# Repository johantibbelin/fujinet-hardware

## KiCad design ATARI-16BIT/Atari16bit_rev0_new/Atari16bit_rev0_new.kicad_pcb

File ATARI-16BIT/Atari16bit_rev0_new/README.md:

# Fujinet Atari 16-bit rev0

Schematic for Atari 16-bit Fujinet prototype. No board layout is done yet.

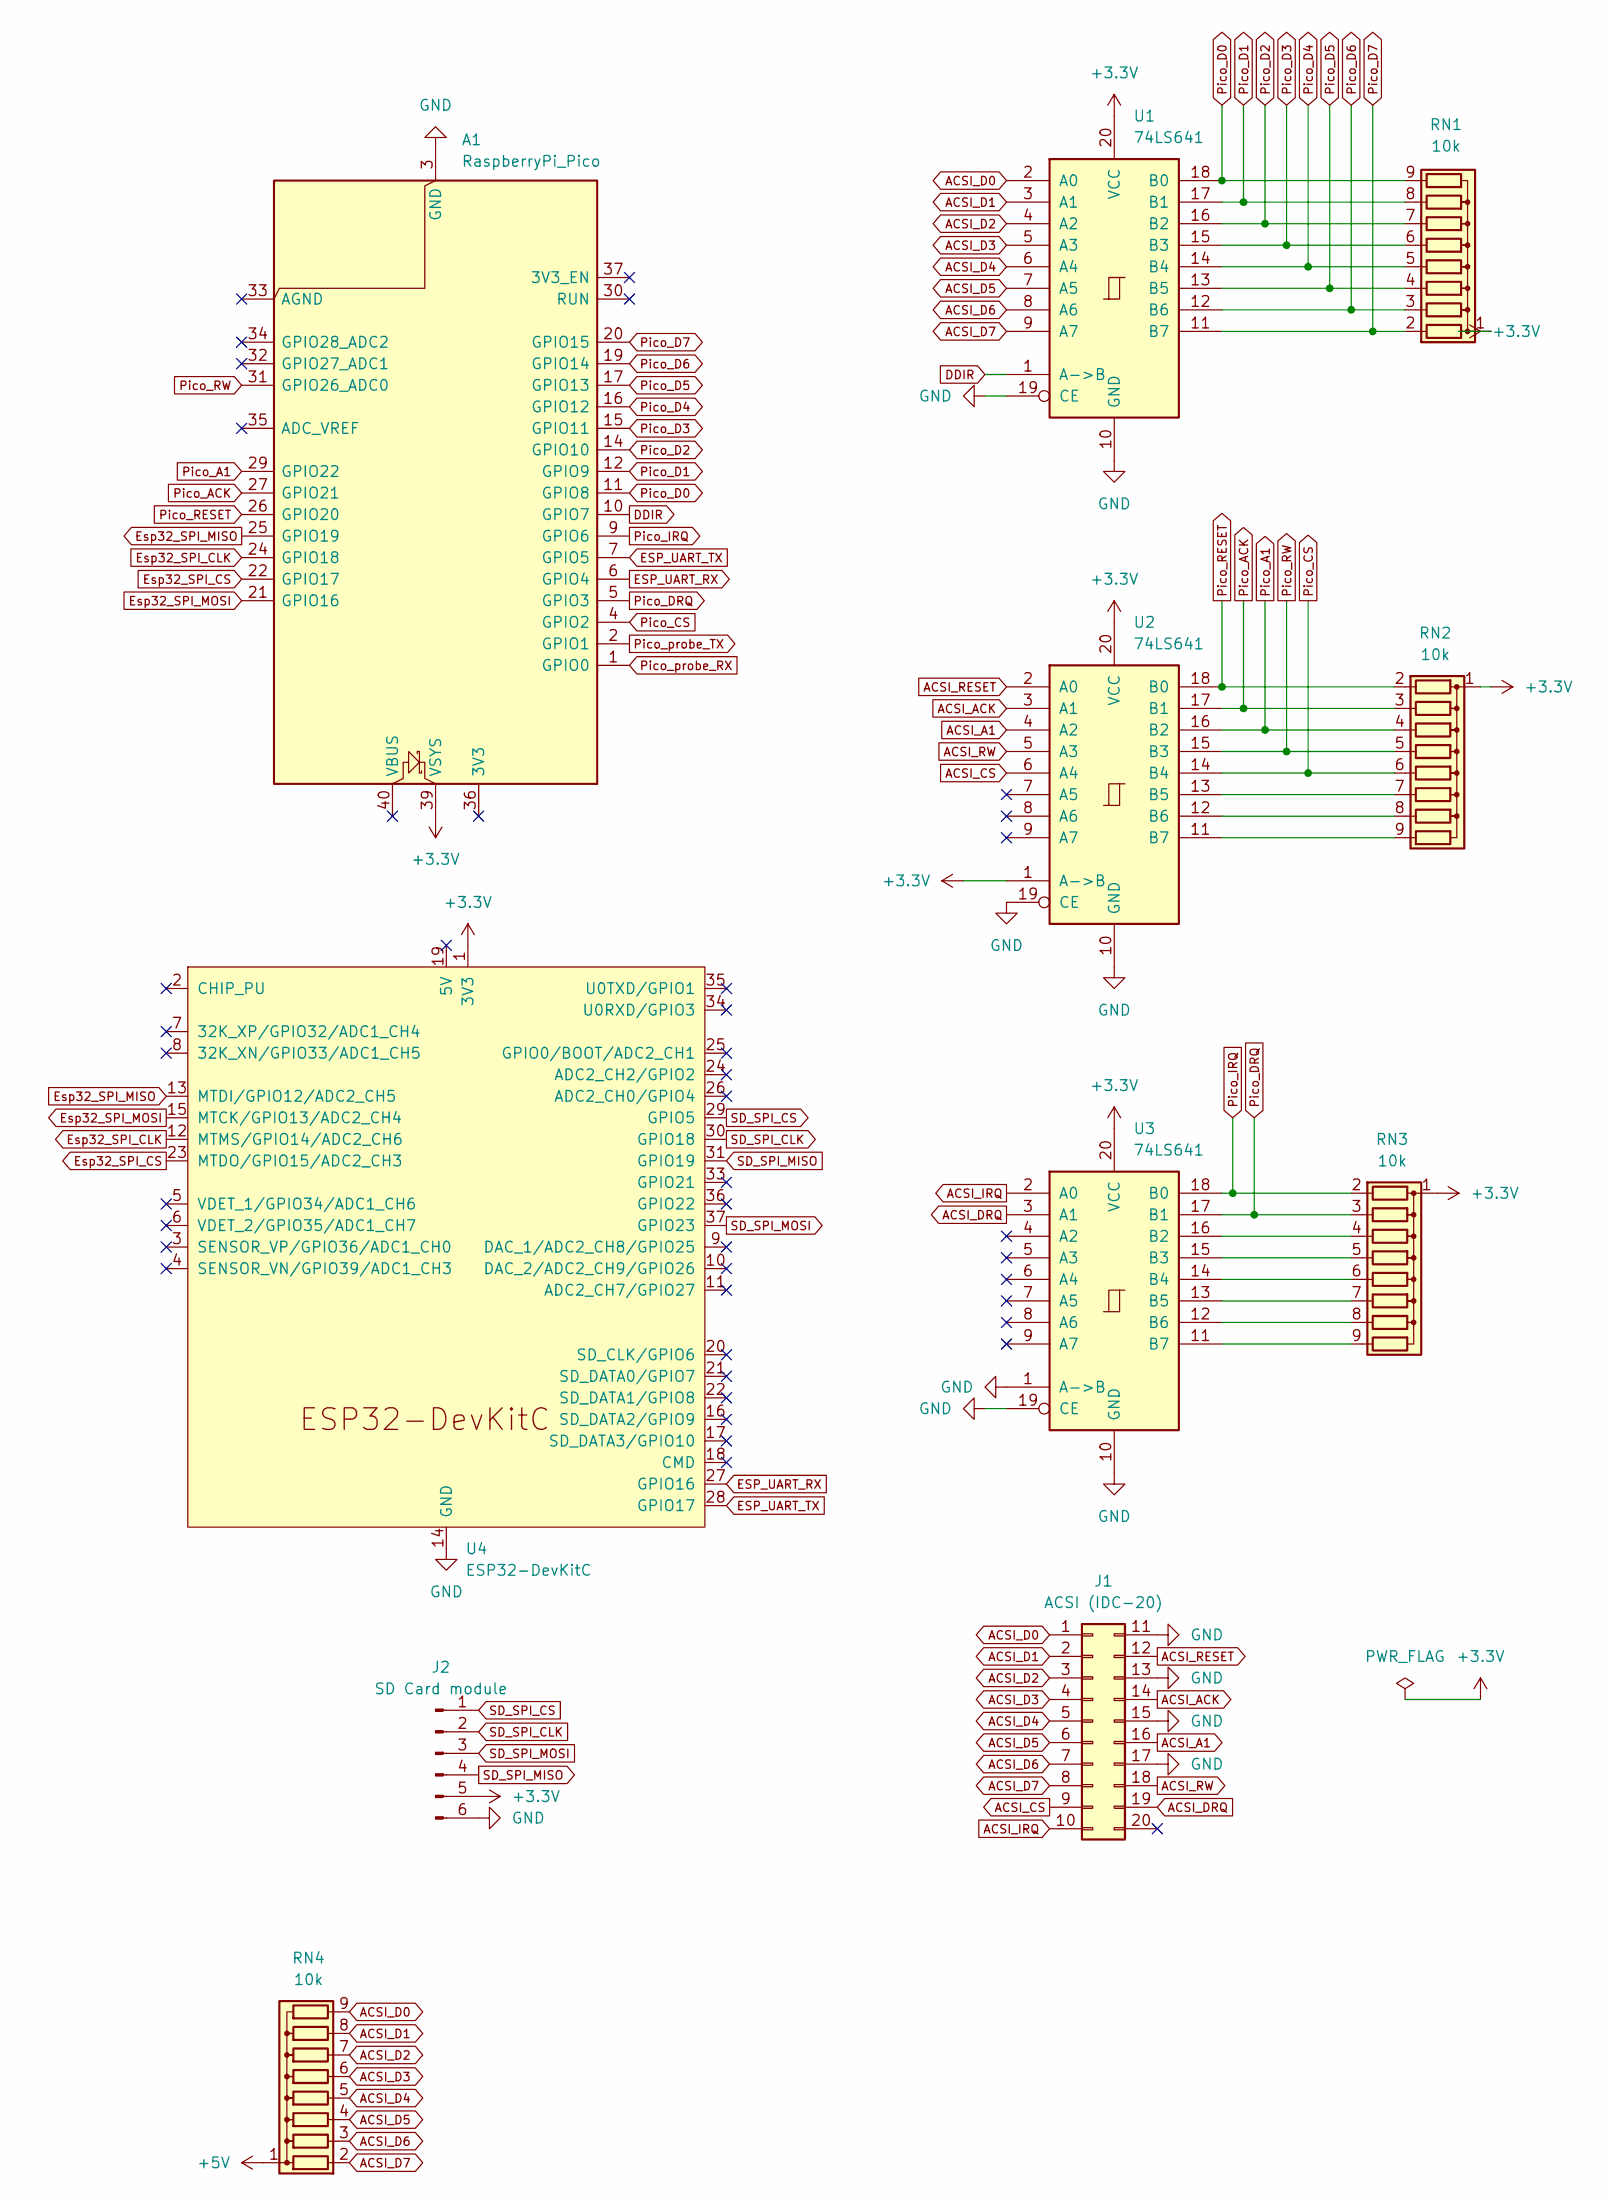
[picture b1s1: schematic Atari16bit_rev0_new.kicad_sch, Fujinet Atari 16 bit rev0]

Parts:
A1: RaspberryPi_Pico; RaspberryPi_Pico_Common_THT
J1: ACSI (IDC-20); Connector_ACSI_IDC
J2: SD Card module; PinHeader_1x06_P2.54mm_Vertical
RN1, RN2, RN3, RN4: 10k; R_Array_SIP9
U1, U2, U3: 74LS641; CERDIP-20_W7.62mm_SideBrazed
U4: ESP32-DevKitC

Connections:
+3.3V: A1.39 (VSYS), J2.5, RN1.1 (common), RN2.1 (common), RN3.1 (common), U1.20 (VCC), U2.1 (A->B), U2.20 (VCC), U3.20 (VCC), U4.1 (3V3)
+5V: RN4.1 (common)
ACSI_A1: J1.16, U2.4 (A2)
ACSI_ACK: J1.14, U2.3 (A1)
ACSI_CS: J1.9, U2.6 (A4)
ACSI_D0: J1.1, RN4.9 (R8), U1.2 (A0)
ACSI_D1: J1.2, RN4.8 (R7), U1.3 (A1)
ACSI_D2: J1.3, RN4.7 (R6), U1.4 (A2)
ACSI_D3: J1.4, RN4.6 (R5), U1.5 (A3)
ACSI_D4: J1.5, RN4.5 (R4), U1.6 (A4)
ACSI_D5: J1.6, RN4.4 (R3), U1.7 (A5)
ACSI_D6: J1.7, RN4.3 (R2), U1.8 (A6)
ACSI_D7: J1.8, RN4.2 (R1), U1.9 (A7)
ACSI_DRQ: J1.19, U3.3 (A1)
ACSI_IRQ: J1.10, U3.2 (A0)
ACSI_RESET: J1.12, U2.2 (A0)
ACSI_RW: J1.18, U2.5 (A3)
DDIR: A1.10 (GPIO7), U1.1 (A->B)
ESP_UART_RX: A1.6 (GPIO4), U4.27 (GPIO16)
ESP_UART_TX: A1.7 (GPIO5), U4.28 (GPIO17)
Esp32_SPI_CLK: A1.24 (GPIO18), U4.12 (MTMS/GPIO14/ADC2_CH6)
Esp32_SPI_CS: A1.22 (GPIO17), U4.23 (MTDO/GPIO15/ADC2_CH3)
Esp32_SPI_MISO: A1.25 (GPIO19), U4.13 (MTDI/GPIO12/ADC2_CH5)
Esp32_SPI_MOSI: A1.21 (GPIO16), U4.15 (MTCK/GPIO13/ADC2_CH4)
GND: A1.3 (GND), A1.8 (GND), A1.13 (GND), A1.18 (GND), A1.23 (GND), A1.28 (GND), A1.38 (GND), J1.11, J1.13, J1.15, J1.17, J2.6, U1.10 (GND), U1.19 (CE), U2.10 (GND), U2.19 (CE), U3.1 (A->B), U3.10 (GND), U3.19 (CE), U4.14 (GND), U4.32 (GND), U4.38 (GND)
unnamed: RN2.7 (R6), U2.13 (B5)
unnamed: RN2.8 (R7), U2.12 (B6)
unnamed: RN2.9 (R8), U2.11 (B7)
unnamed: RN3.4 (R3), U3.16 (B2)
unnamed: RN3.5 (R4), U3.15 (B3)
unnamed: RN3.6 (R5), U3.14 (B4)
unnamed: RN3.7 (R6), U3.13 (B5)
unnamed: RN3.8 (R7), U3.12 (B6)
unnamed: RN3.9 (R8), U3.11 (B7)
Pico_A1: A1.29 (GPIO22), RN2.4 (R3), U2.16 (B2)
Pico_ACK: A1.27 (GPIO21), RN2.3 (R2), U2.17 (B1)
Pico_CS: A1.4 (GPIO2), RN2.6 (R5), U2.14 (B4)
Pico_D0: A1.11 (GPIO8), RN1.9 (R8), U1.18 (B0)
Pico_D1: A1.12 (GPIO9), RN1.8 (R7), U1.17 (B1)
Pico_D2: A1.14 (GPIO10), RN1.7 (R6), U1.16 (B2)
Pico_D3: A1.15 (GPIO11), RN1.6 (R5), U1.15 (B3)
Pico_D4: A1.16 (GPIO12), RN1.5 (R4), U1.14 (B4)
Pico_D5: A1.17 (GPIO13), RN1.4 (R3), U1.13 (B5)
Pico_D6: A1.19 (GPIO14), RN1.3 (R2), U1.12 (B6)
Pico_D7: A1.20 (GPIO15), RN1.2 (R1), U1.11 (B7)
Pico_DRQ: A1.5 (GPIO3), RN3.3 (R2), U3.17 (B1)
Pico_IRQ: A1.9 (GPIO6), RN3.2 (R1), U3.18 (B0)
Pico_RESET: A1.26 (GPIO20), RN2.2 (R1), U2.18 (B0)
Pico_RW: A1.31 (GPIO26_ADC0), RN2.5 (R4), U2.15 (B3)
Pico_probe_RX: A1.1 (GPIO0)
Pico_probe_TX: A1.2 (GPIO1)
SD_SPI_CLK: J2.2, U4.30 (GPIO18)
SD_SPI_CS: J2.1, U4.29 (GPIO5)
SD_SPI_MISO: J2.4, U4.31 (GPIO19)
SD_SPI_MOSI: J2.3, U4.37 (GPIO23)

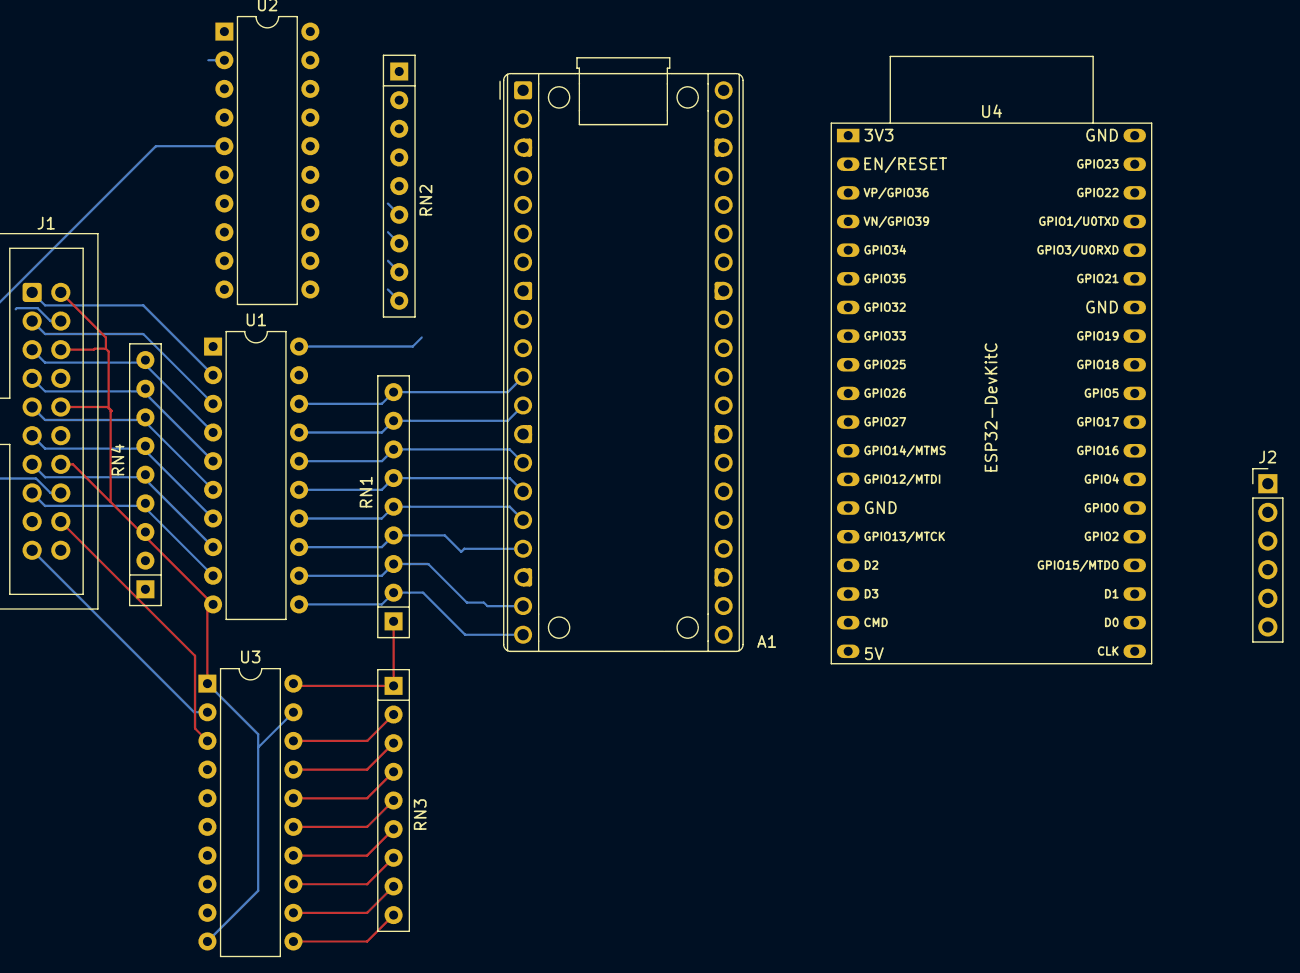
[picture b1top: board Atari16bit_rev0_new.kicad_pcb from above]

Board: 2 copper layers, 11 parts (0 on the bottom side), 52 nets.

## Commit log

2024-07-03 Start
2024-10-13 Fixed signal label error ACSI_DRQ
2024-10-13 File restructure
2024-10-13 [Atari16bit] rev0 schematic completed
2024-10-13 [Atari16bit] rev0 schematic
    Start
    [Atari16bit] rev0 schematic completed
    File restructure
2024-10-15 Schematic now passes ERC
    Added PWR_FLAG
2025-01-17 [Atari16bit] Schematic update
    pcb WIP
2025-02-06 [Atari16bit] Updates
    Updated: Pins of Pico, Added UART from pico to esp32 and added 5V pullup on databus.
2025-02-06 [Atari16bit] PCB update WIP
